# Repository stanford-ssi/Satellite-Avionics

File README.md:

# Satellite-Avionics

Welcome to SSI **Satellite Avionics**! Here, you can find everything you need to navigate our team! This repository covers weekly meeting times, technical trainings, team design documentation, assembly processes, testing procedures, and so much more!

**If you're new to Satellite Avionics, (and of course, are a stanford student), you should look through the [Satellite Avionics Onboarding Document](https://docs.google.com/document/d/1Evk9vAAE3cXXHKh05v-SdmLuFbIsvqwTA4ssfbo16VE/edit?tab=t.0) to get started on our team!**

If you have any questions, feel free to contact any AV Co-lead on Slack! Or feel free to email Kale, the current AV co-lead repo manager at **kalesrz@stanford.edu**.

# Current Leadership (Spring 2026 - Winter 2027)
Satellite Avionics Co-Leads: 
 * Clara Zhen (czhen@stanford.edu)
 * Nimalan Anbhuarasan (nimalan@stanford.edu)
 * Kale Suarez (kalesrz@stanford.edu)

Satellite Co-Leads: 
 * Amy Zheng (amyzheng@stanford.edu)
 * River Dowdy (rivdowdy@stanford.edu)
 * Carson Lauer (clauer@stanford.edu)

Workspace Manager: Clara Zhen
 - Contact For Questions Regarding ES3 and Durand Access

## Getting On Slack!
In order to join our weekly meetings, you'll need to join our slack to figure out where were meeting! You can join our slack by clicking [here](https://ssi-teams.slack.com/signup). Once you're on the slack, go ahead and add the [#satellite-avionics](https://ssi-teams.slack.com/archives/C2L29KW8J) channel. You should also make sure to join all of these important channels!
* [#satellite-avionics](https://ssi-teams.slack.com/archives/C2L29KW8J)
    - All AV communication and announcements happen here! You need to be in this channel to know
      where were meeting for the week.
* [#satellites](https://ssi-teams.slack.com/archives/C04JL94F9)
    - General Satellites team communications and announcements happen here!
* [#satellite-systems](https://ssi-teams.slack.com/archives/C4UL92684)
    - System-wide meeting plans and discussions with other subteams on Satellites happen here!
* [#esiii](https://ssi-teams.slack.com/archives/C3YLQTN87)
    - Our Lab Space!!!
* [#doorbell](https://ssi-teams.slack.com/archives/CE360LHD0)
    - If you don't have keycard access to End Station III (ES3), run the `\doorbell` command to get someone to come open the door if anyones in ES3.

## Weekly Meeting Times
Satellite Avionics has two official meetings each week:
**Weekly Avionics Meeting**
 * **Time:** Wednesday, 7:00 PM - 9:00 PM PST
 * **Location:** Check The [#Satellite-Avionics](https://ssi-teams.slack.com/archives/C2L29KW8J) channel in the slack for weekly meeting locations!
 * **Purpose:** Avionics meetings are specifically for AV-specific work, training, and discussions. AV member attendance is expected outside of conflicting Midterms or Finals. Fall quarter attendance is **mandatory** outside of class conflicts or personal health reasons.

**Satsurday Meetings**
 * **Time:** Saturday, 12:00 PM - 2:00 PM PST
 * **Location:** Check The [#Satellite-Avionics](https://ssi-teams.slack.com/archives/C2L29KW8J) channel in the slack for weekly meeting locations!
 * **Purpose**: Satsurday meetings are Satellite Avionics Full-Team work days! Every subteam will be meeting at this time. This can sometimes happen collectively and sometimes separately. Fall quarter will mostly be dedicated to AV specific onboarding training and early satellite development. Fall quarter attendance is **mandatory** outside of class conflicts or personal health reasons.

**Systems Meeting**
 * **Time:** Wednesday, 7:00 PM - 9:00 PM PST
 * **Location:** Check The [#Satellite-Systems](https://ssi-teams.slack.com/archives/C4UL92684) channel in the slack for weekly meeting locations!
 * **Purpose:** Systems meetings are where all major decisions about our satellite design occur and system-level planning and cross-team collaboration is planned. You are not obligated to come to these meetings if you are unable to, however, you should come to these meetings if you are available.

## Accessing Our Workspaces!
We primarily operate out of two buildings, End Station III (Deep Lab / Hepl South), and the Durand Aeronautics & Astronautics building. End Station III is a little difficult to find the first time, so please ask leads in the slack if you get lost!

### End Station III (Deep Lab / Hepl South)
**Address:** 491 S Service Rd, Stanford, CA 94305\
**Google Maps Link:** [Stanford Student Space Initiative](https://maps.app.goo.gl/ZUDnvgVmYYjSPFpS8)\
**Access Entrance:** Please enter through the **North Entrance** on Service Road (As Seen Below). After-Hours/Weekend Access requires that you obtain keycard access.

### Stanford University Aeronautics & Astronautics (Durand)
**Address:** 496 Lomita Mall, Stanford, CA 94305\
**Google Maps Link:** [Stanford University Aeronautics & Astronautics (Durand)](https://maps.app.goo.gl/TxbG7z5m1ypoC3tW7)\
**Access Entrance:** Any entrance can be used given you have obtained Durand keycard access. Otherwise, feel free to message a lead in the [#satellite-avionics](https://ssi-teams.slack.com/archives/C2L29KW8J) slack channel if you need help getting in!

### Gaining Access
To be able to gain keycard access to these workspaces and to be able to enter without another member to scan you in, you must complete the ES3 Lab safety trainings and complete all the steps listed on the [ES3 Access Guide](https://sites.google.com/stanford.edu/ssi/end-station-iii/keycard-access-for-es3). You will need to use your Stanford Email in order to view the guide.

## Additional Helpful Links / Quick Access
* [Stanford SSI Wiki: Satellites](https://ssi-wiki.stanford.edu/Category:Satellites)
    * SSI's official wiki page (notice: sometimes outdated, but there is some pretty useful information about the team and important definitions if you'd like to check it out.)\
* [SSI Slack Signup](https://ssi-teams.slack.com/signup)
* [ES3 Access Guide](https://sites.google.com/stanford.edu/ssi/end-station-iii/keycard-access-for-es3)

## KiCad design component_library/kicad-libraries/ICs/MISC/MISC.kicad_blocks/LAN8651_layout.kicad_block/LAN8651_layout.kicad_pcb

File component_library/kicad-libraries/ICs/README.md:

# ICs — design blocks by subsystem

Reusable KiCad 10 schematic **design blocks** for ICs, organized by subsystem. Each block contains
the IC together with its supporting passives and connections (the full application circuit), plus a
README explaining what the IC does and how the block is wired. Datasheets live in
[`component_library/datasheets-only/ICs/`](../../datasheets-only/ICs/).

| Subsystem | Folder | Contents |
|-----------|--------|----------|
| TT&C (Telemetry, Tracking & Command) | [`TT&C/`](TT%26C/) | Radios, radio power, antenna balun and ground-station RF switching, taken from SAMWISE |
| POWER | [`POWER/`](POWER/) | Power converters taken from SAMWISE (TPS54426 5 V buck) |

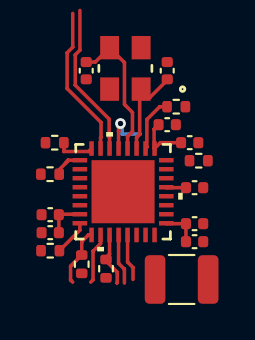
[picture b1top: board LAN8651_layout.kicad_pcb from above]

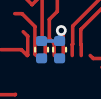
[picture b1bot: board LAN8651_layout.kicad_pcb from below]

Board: 2 copper layers, 21 parts (2 on the bottom side), 12 nets.

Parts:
C1: 10uF; C_1210_3225Metric
C2, C3, C9, C12: 100nF; C_0402_1005Metric
C4, C5, C6, C7: 10nF; C_0402_1005Metric
C8, C11: 27pF; C_0402_1005Metric
C10: 4.7uF; C_0402_1005Metric
R1, R3, R4, R5, R6, R7: 10kΩ; R_0402_1005Metric
R2: 12.4Ω; R_0402_1005Metric
U1: LAN8651B1-E/LMX; VQFN32_LMX_MCH
Y1: 25 MHz; CRYSTAL_ABM8G_ABR

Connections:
+3V3: C1.1, C2.1, C3.1, C4.1, C5.1, C6.1, C7.1, C9.1, C12.1, R7.1, U1.4 (TEST), U1.7 (VDDP), U1.17 (VDDP), U1.25 (VDDAU), U1.29 (VDDA)
/CCOMP: C10.1, U1.21 (CCOMP)
/CS_N: R4.1, U1.11 (CS_N)
/IN_H: R1.1, U1.1 (INH)
/IRQ_N: R6.1, U1.9 (IRQ_N)
/RESET_N: R3.1, U1.8 (RESET_N)
/WAKE_IN: R7.2, U1.32 (WAKE_IN)
/WAKE_OUT: R5.1, U1.24 (WAKE_OUT)
GND: C1.2, C2.2, C3.2, C4.2, C5.2, C6.2, C7.2, C8.2, C9.2, C10.2, C11.2, C12.2, R1.2, R2.1, R3.2, R4.2, R5.2, R6.2, U1.2 (VSS), U1.3 (VSS), U1.5 (VSS), U1.14 (DIOB1), U1.16 (DIOB0), U1.18 (DIOA0), U1.19 (DIOA1), U1.20 (DIOA2), U1.22 (DIOA3), U1.23 (DIOA4), U1.33 (VSS), Y1.2 (G), Y1.4 (G)
unnamed: R2.2, U1.26 (RBIAS)
unnamed: C8.1, U1.27 (XTI), Y1.1
unnamed: C11.1, U1.28 (XTO), Y1.3
